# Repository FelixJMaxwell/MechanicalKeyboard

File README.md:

# Teclados Mecanicos
Repositorio creado para contener proyectos relacionados al super costoso hobby de los teclados mecanicos.

Siguiendo los tutoriales por parte de ai03 y MasterZen
 - [PCB Designer Guide](https://wiki.ai03.com/books/pcb-design/chapter/pcb-designer-guide)
 - [Designing a keyboard from scratch](https://www.masterzen.fr/2020/05/03/designing-a-keyboard-part-1/)

No considero ninguna de los dos anterior mejor que el otro pues se complementan en diferentes aspectos.

<br>
<br>
  
# Macropad

Foot print con marca para cada tecla  
  
Footprint sin marca para cada tecla  

<br>
<br>
  
# Split keyboard

<br>
<br>

# Cuarenta Keyboard

La PCB anterior contiene tres errores

1.- Un switch no esta conectado al diodo correspondiente

2.- Hizo falta poner una via para conectar tres switches a su columna correspondiente

3.- El encoder esta conectado en la misma posicion del ultimo switch de su columna, se de agregar a una nueva fila.

Esta PCB la envie a producción con JLCPCB antes de ver los errores por lo que llegaron cinco placas todas con los tres errores anteriores.

Errores en la PCB, corregidos con puentes usando barillas de laton.

Encoder + switch conectado a otro pin del Arduino micro al mismo tiempo que se puentean los adaptadores para hotswap 

Se conecta el adaptador hotswap al diodo correspondiente

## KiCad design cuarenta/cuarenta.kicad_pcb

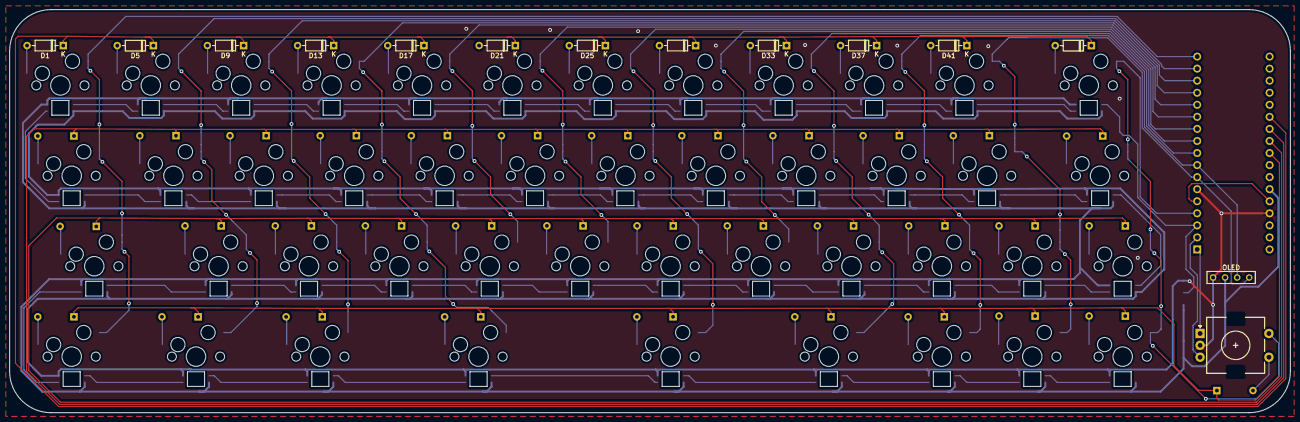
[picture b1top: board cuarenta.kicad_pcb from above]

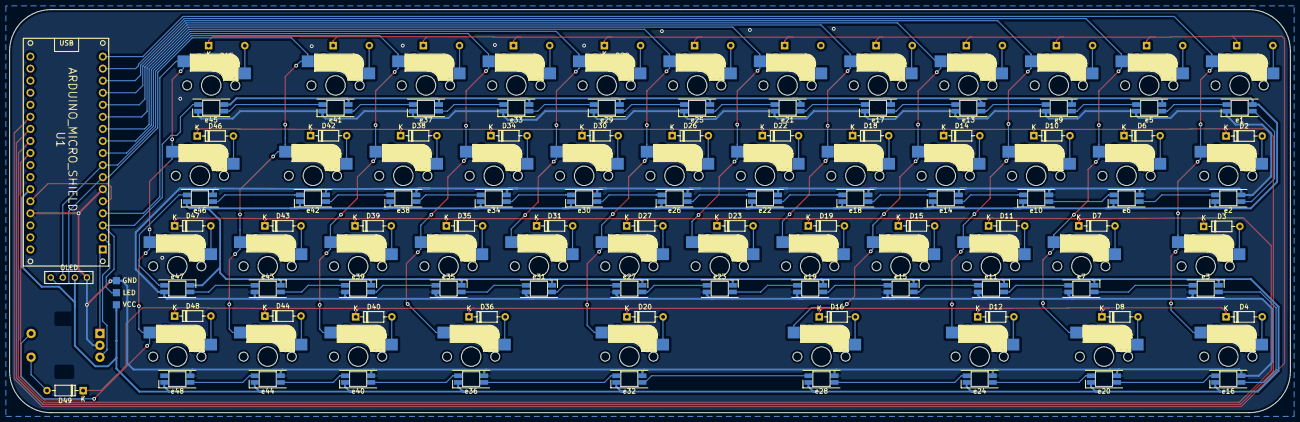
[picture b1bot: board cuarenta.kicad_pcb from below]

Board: 2 copper layers, 269.8 x 84.9 mm, 140 parts (81 on the bottom side), 111 nets.

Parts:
D1, D2, D3, D4, D5, D6, D7, D8, D9, D10, D11, D12, D13, D14, D15, D16, D17, D18, D19, D20, D21, D22, D23, D25, D26, D27, D29, D30, D31, D33, D34, D35, D36, D37, D38, D39, D40, D41, D42, D43, D44, D45, D46, D47, D48, D49: 1N4148; D_DO-35_SOD27_P7.62mm_Horizontal
J1: LED; StripLED_1side
OL1: OLED
SW1, SW2, SW3, SW4, SW5, SW6, SW7, SW8, SW9, SW10, SW11, SW12, SW13, SW14, SW15, SW16, SW17, SW18, SW19, SW20, SW21, SW22, SW23, SW25, SW26, SW27, SW29, SW30, SW31, SW33, SW34, SW35, SW36, SW37, SW38, SW39, SW40, SW41, SW42, SW43, SW44, SW45, SW46, SW47, SW48: SW_Push; CherryMX_Hotswap
SW49: Rotary_Encoder_Switch; RotaryEncoder_EC11
U1: ARDUINO_MICRO_SHIELD
e1, e2, e3, e5, e6, e7, e9, e10, e11, e13, e14, e15, e16, e17, e18, e19, e20, e21, e22, e23, e24, e25, e26, e27, e28, e29, e30, e31, e32, e33, e34, e35, e36, e37, e38, e39, e40, e41, e42, e43, e44, e45, e46, e47, e48: e; YS-SK6812MINI-E_2

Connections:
Col0: SW1.2, SW2.2, SW3.2, SW4.2, U1.12
Col1: SW5.2, SW6.2, SW7.2, SW8.2, U1.11
Col2: SW9.2, SW10.2, SW11.2, SW12.2, U1.10
Col3: SW13.2, SW14.2, SW15.2, SW16.2, U1.9
Col4: SW17.2, SW18.2, SW19.2, U1.8
Col5: SW21.2, SW22.2, SW23.2, U1.7
Col6: SW20.2, SW25.2, SW26.2, SW27.2, U1.6
Col7: SW29.2, SW30.2, SW31.2, U1.5
Col8: SW33.2, SW34.2, SW35.2, SW36.2, U1.4
Col9: OL1.3, SW37.2, SW38.2, SW39.2, SW40.2, U1.3
Col10: OL1.4, SW41.2, SW42.2, SW43.2, SW44.2, U1.2
Col11: SW45.2, SW46.2, SW47.2, SW48.2, SW49.S2, U1.RX
GND: J1.3, OL1.1, SW49.C, U1.GND, e1.3, e2.1, e3.1, e5.3, e6.1, e7.1, e9.3, e10.1, e11.1, e13.3, e14.1, e15.1, e16.1, e17.3, e18.1, e19.1, e20.1, e21.3, e22.1, e23.1, e24.1, e25.3, e26.1, e27.1, e28.1, e29.3, e30.1, e31.1, e32.1, e33.3, e34.1, e35.1, e36.1, e37.3, e38.1, e39.1, e40.1, e41.3, e42.1, e43.1, e44.1, e45.3, e46.1, e47.1, e48.1
LED: J1.2, U1.TX, e45.4
unnamed: D1.2, SW1.1
unnamed: D2.2, SW2.1
unnamed: D3.2, SW3.1
unnamed: D4.2, SW4.1
unnamed: D5.2, SW5.1
unnamed: D6.2, SW6.1
unnamed: D7.2, SW7.1
unnamed: D8.2, SW8.1
unnamed: D9.2, SW9.1
unnamed: D10.2, SW10.1
unnamed: D11.2, SW11.1
unnamed: D12.2, SW12.1
unnamed: D13.2, SW13.1
unnamed: D14.2, SW14.1
unnamed: D15.2, SW15.1
unnamed: D16.2, SW16.1
unnamed: D17.2, SW17.1
unnamed: D18.2, SW18.1
unnamed: D19.2, SW19.1
unnamed: D20.2, SW20.1
unnamed: D21.2, SW21.1
unnamed: D22.2, SW22.1
unnamed: D23.2, SW23.1
unnamed: D25.2, SW25.1
unnamed: D26.2, SW26.1
unnamed: D27.2, SW27.1
unnamed: D29.2, SW29.1
unnamed: D30.2, SW30.1
unnamed: D31.2, SW31.1
unnamed: D33.2, SW33.1
unnamed: D34.2, SW34.1
unnamed: D35.2, SW35.1
unnamed: D36.2, SW36.1
unnamed: D37.2, SW37.1
unnamed: D38.2, SW38.1
unnamed: D39.2, SW39.1
unnamed: D40.2, SW40.1
unnamed: D41.2, SW41.1
unnamed: D42.2, SW42.1
unnamed: D43.2, SW43.1
unnamed: D44.2, SW44.1
unnamed: D45.2, SW45.1
unnamed: D46.2, SW46.1
unnamed: D47.2, SW47.1
unnamed: D48.2, SW48.1
unnamed: D49.2, SW49.S1
unnamed: e1.2, e2.2
unnamed: e1.4, e5.2
unnamed: e2.4, e6.2
unnamed: e3.2, e7.4
unnamed: e5.4, e9.2
unnamed: e6.4, e10.2
unnamed: e10.4, e14.2
unnamed: e11.2, e15.4
unnamed: e7.2, e11.4
unnamed: e9.4, e13.2
unnamed: e13.4, e17.2
unnamed: e14.4, e18.2
unnamed: e15.2, e19.4
unnamed: e3.4, e16.2
unnamed: e16.4, e20.2
unnamed: e17.4, e21.2
unnamed: e18.4, e22.2
unnamed: e19.2, e23.4
unnamed: e20.4, e24.2
unnamed: e21.4, e25.2
unnamed: e22.4, e26.2
unnamed: e23.2, e27.4
unnamed: e24.4, e28.2
unnamed: e25.4, e29.2
unnamed: e26.4, e30.2
unnamed: e27.2, e31.4
unnamed: e28.4, e32.2
unnamed: e29.4, e33.2
unnamed: e30.4, e34.2
unnamed: e31.2, e35.4
unnamed: e32.4, e36.2
unnamed: e33.4, e37.2
unnamed: e34.4, e38.2
unnamed: e35.2, e39.4
unnamed: e36.4, e40.2
unnamed: e37.4, e41.2
unnamed: e38.4, e42.2
unnamed: e39.2, e43.4
unnamed: e40.4, e44.2
unnamed: e41.4, e45.2
unnamed: e42.4, e46.2
unnamed: e43.2, e47.4
unnamed: e44.4, e48.2
unnamed: e46.4, e47.2
Row0: D1.1, D5.1, D9.1, D13.1, D17.1, D21.1, D25.1, D29.1, D33.1, D37.1, D41.1, D45.1, U1.A2
Row1: D2.1, D6.1, D10.1, D14.1, D18.1, D22.1, D26.1, D30.1, D34.1, D38.1, D42.1, D46.1, U1.A3
Row2: D3.1, D7.1, D11.1, D15.1, D19.1, D23.1, D27.1, D31.1, D35.1, D39.1, D43.1, D47.1, U1.A4
Row3: D4.1, D8.1, D12.1, D16.1, D20.1, D36.1, D40.1, D44.1, D48.1, D49.1, U1.A5
VCC: J1.1, OL1.2, U1.5V, e1.1, e2.3, e3.3, e5.1, e6.3, e7.3, e9.1, e10.3, e11.3, e13.1, e14.3, e15.3, e16.3, e17.1, e18.3, e19.3, e20.3, e21.1, e22.3, e23.3, e24.3, e25.1, e26.3, e27.3, e28.3, e29.1, e30.3, e31.3, e32.3, e33.1, e34.3, e35.3, e36.3, e37.1, e38.3, e39.3, e40.3, e41.1, e42.3, e43.3, e44.3, e45.1, e46.3, e47.3, e48.3
en1: SW49.B, U1.SS
en2: SW49.A, U1.MO

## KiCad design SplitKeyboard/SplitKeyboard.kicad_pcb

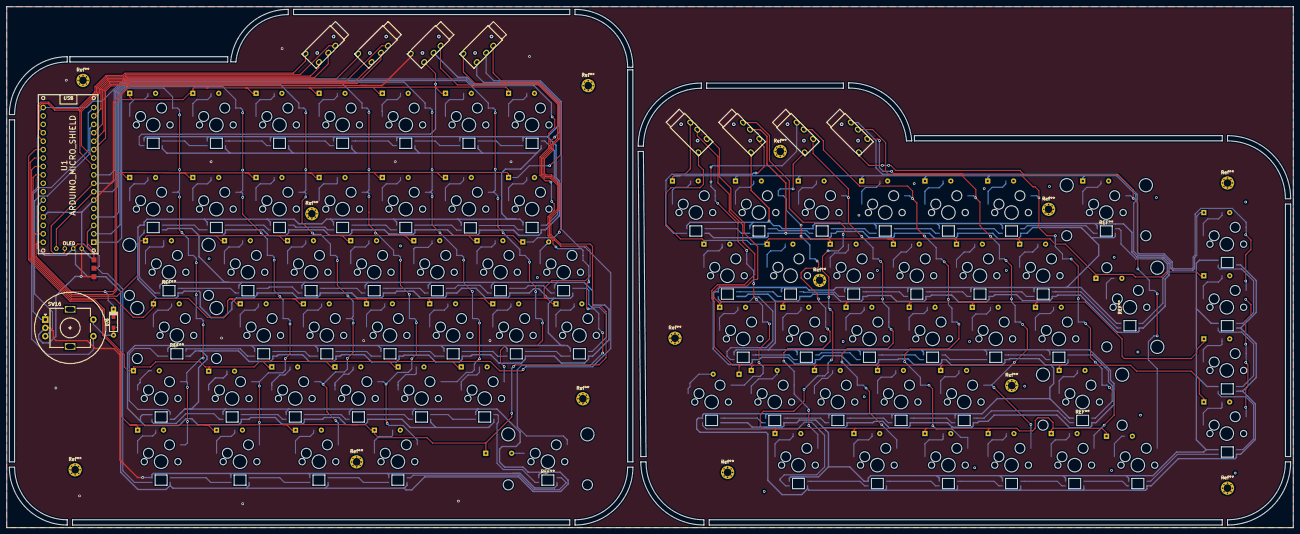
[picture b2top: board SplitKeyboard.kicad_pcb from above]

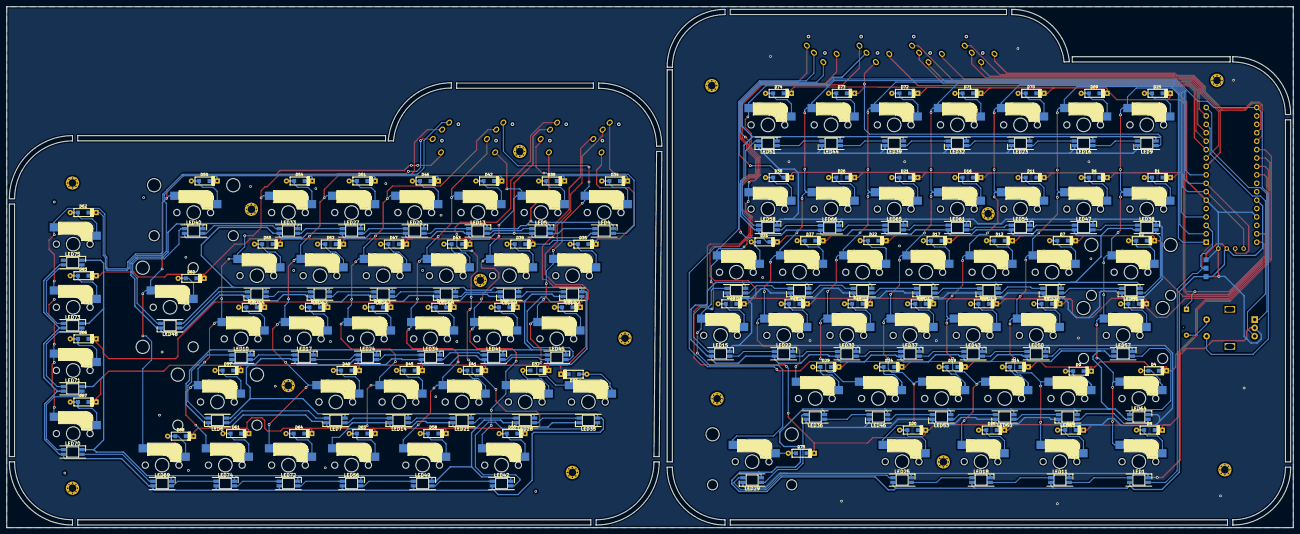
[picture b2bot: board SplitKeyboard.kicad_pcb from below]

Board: 2 copper layers, 388.1 x 157.1 mm, 252 parts (150 on the bottom side), 105 nets.

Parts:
D1, D2, D3, D4, D5, D6, D7, D8, D9, D10, D11, D12, D13, D14, D15, D16, D17, D18, D19, D20, D21, D22, D23, D24, D25, D26, D27, D28, D29, D30, D31, D32, D33, D34, D35, D36, D37, D38, D39, D40, D41, D42, D43, D44, D45, D46, D47, D48, D49, D50, D51, D52, D53, D54, D55, D56, D57, D58, D59, D60, D61, D62, D63, D64, D65, D66, D67, D68, D69, D70, D71, D72, D73, D74, D75, D76: 1N4148; D_SOD123_axial
J1: LED; StripLED_rev
JTRRS1, JTRRS2, JTRRS3, JTRRS4, JTRRS5, JTRRS6, JTRRS7, JTRRS8: 4PIN; TRRS-PJ-320A
LED1, LED2, LED3, LED4, LED5, LED6, LED7, LED8, LED9, LED10, LED11, LED12, LED13, LED14, LED15, LED16, LED17, LED18, LED19, LED20, LED21, LED22, LED23, LED24, LED25, LED26, LED27, LED28, LED29, LED30, LED31, LED32, LED33, LED34, LED35, LED36, LED37, LED38, LED39, LED40, LED41, LED42, LED43, LED44, LED45, LED46, LED47, LED48, LED49, LED50, LED51, LED52, LED53, LED54, LED55, LED56, LED57, LED58, LED59, LED60, LED61, LED62, LED63, LED64, LED65, LED66, LED67, LED68, LED69, LED70, LED71, LED72, LED73, LED74, LED75: YS-SK6812MINI-E; YS-SK6812MINI-E_2
P2: OLED; OLED_v2
Ref**: Val**; M2_HOLE_v3
Ref**#2, Ref**#3, Ref**#4, Ref**#5, Ref**#6, Ref**#7, Ref**#8, Ref**#9, Ref**#10, Ref**#11, Ref**#12, Ref**#13, Ref**#14: Val**; M2_HOLE_v3
SW0, SW1, SW2, SW3, SW4, SW5, SW6, SW7, SW8, SW9, SW14, SW15: SW_Push; CherryMX_Hotswap
SW10: SW_DownArrow; CherryMX_Hotswap
SW13: SW_RightArrow; CherryMX_Hotswap
SW16: Rotary_Encoder_Switch; RotaryEncoder_Alps_EC11E-Switch_Vertical_H20mm
SW+1: SW_Push; CherryMX_Hotswap
SWBarrita1: SW_Push; CherryMX_Hotswap
SWCtrlright1: SW_Push; CherryMX_Hotswap
SWF2, SWF4, SWF5, SWF6, SWF8, SWF12: SW_Push; CherryMX_Hotswap
SWLeftArrow1: SW_Push; CherryMX_Hotswap
SWUpArrow1: SW_Push; CherryMX_Hotswap
SWa1: SW_Push; CherryMX_Hotswap
SWaltgr1: SW_Push; CherryMX_Hotswap
SWaltleft1: SW_Push; CherryMX_Hotswap
SWb1: SW_Push; CherryMX_Hotswap
SWbackslash1: SW_Push; CherryMX_Hotswap
SWbloqmayus1: SW_Push; CherryMX_Hotswap
SWc1: SW_Push; CherryMX_Hotswap
SWcomilla1: SW_Push; CherryMX_Hotswap
SWcomma1: SW_Push; CherryMX_Hotswap
SWctrl1: SW_Push; CherryMX_Hotswap
SWd1: SW_Push; CherryMX_Hotswap
SWe1: SW_Push; CherryMX_Hotswap
SWend1: SW_Push; CherryMX_Hotswap
SWenter1: SW_Push; CherryMX_Hotswap
SWesc1: SW_Push; CherryMX_Hotswap
SWf1: SW_Push; CherryMX_Hotswap
SWfn1: SW_Push; CherryMX_Hotswap
SWg1: SW_Push; CherryMX_Hotswap
SWguion1: SW_Push; CherryMX_Hotswap
SWh1: SW_Push; CherryMX_Hotswap
SWhome1: SW_Push; CherryMX_Hotswap
SWi1: SW_Push; CherryMX_Hotswap
SWj1: SW_Push; CherryMX_Hotswap
SWk1: SW_Push; CherryMX_Hotswap
SWl1: SW_Push; CherryMX_Hotswap
SWm1: SW_Push; CherryMX_Hotswap
SWn1: SW_Push; CherryMX_Hotswap
SWo1: SW_Push; CherryMX_Hotswap
SWp1: SW_Push; CherryMX_Hotswap
SWpgdown1: SW_Push; CherryMX_Hotswap
SWpgup1: SW_Push; CherryMX_Hotswap
SWpunto1: SW_Push; CherryMX_Hotswap
SWq1: SW_Push; CherryMX_Hotswap
SWr1: SW_Push; CherryMX_Hotswap
SWs1: SW_Push; CherryMX_Hotswap
SWshift1: SW_Push; CherryMX_Hotswap
SWshiftright1: SW_Push; CherryMX_Hotswap
SWsigno1: SW_Push; CherryMX_Hotswap
SWspace1: SW_Push; CherryMX_Hotswap
SWt1: SW_Push; CherryMX_Hotswap
SWtab1: SW_Push; CherryMX_Hotswap
SWu1: SW_Push; CherryMX_Hotswap
SWv1: SW_Push; CherryMX_Hotswap
SWw1: SW_Push; CherryMX_Hotswap
SWwin1: SW_Push; CherryMX_Hotswap
SWx1: SW_Push; CherryMX_Hotswap
SWy1: SW_Push; CherryMX_Hotswap
SWz1: SW_Push; CherryMX_Hotswap
SW{1: SW_Push; CherryMX_Hotswap
SW}1: SW_Push; CherryMX_Hotswap
U1: ARDUINO_MICRO_SHIELD

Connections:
Columna2: JTRRS4.1, U1.A1
Columna3: JTRRS4.2, U1.5
Columna4: JTRRS4.3, U1.6
Columna5: JTRRS3.3, U1.7
Columna6: JTRRS3.2, U1.8
Columna7: JTRRS3.1, U1.11
Columna8: JTRRS3.4, U1.9
Columna9: SW6.2, SW16.S1, SWF12.2, SWh1.2, SWspace1.2, SWy1.2, U1.13
Columna10: SW5.2, SWF8.2, SWb1.2, SWg1.2, SWt1.2, U1.4
Columna11: P2.2, SW4.2, SWF6.2, SWf1.2, SWr1.2, SWv1.2, U1.3
Columna12: P2.1, SW3.2, SWF5.2, SWc1.2, SWd1.2, SWe1.2, SWfn1.2, U1.2
Columna13: SW2.2, SWF4.2, SWaltleft1.2, SWs1.2, SWw1.2, SWx1.2, U1.RX
Columna14: SW1.2, SWF2.2, SWa1.2, SWq1.2, SWwin1.2, SWz1.2, U1.SS
Columna15: SWBarrita1.2, SWbloqmayus1.2, SWctrl1.2, SWesc1.2, SWshift1.2, SWtab1.2, U1.MO
Columna16: JTRRS4.4, U1.A0
Fila0: D25.1, D69.1, D70.1, D71.1, D72.1, D73.1, D74.1, D76.1, U1.SCK
Fila1: D1.1, D6.1, D11.1, D16.1, D21.1, D26.1, D30.1, JTRRS5.4, U1.MI
Fila3: D3.1, D8.1, D13.1, D18.1, D23.1, D28.1, D32.1, JTRRS5.2, U1.A4
Fila4: D4.1, D9.1, D14.1, D19.1, D24.1, D29.1, JTRRS5.3, U1.A3
Fila5: D5.1, D10.1, D15.1, D20.1, D75.1, JTRRS6.4, U1.A2
Fila6: D2.1, D7.1, D12.1, D17.1, D22.1, D27.1, D31.1, JTRRS5.1, U1.A5
GND: J1.3, JTRRS6.1, LED1.3, LED2.3, LED3.3, LED8.3, LED9.3, LED11.3, LED12.3, LED15.3, LED16.3, LED18.3, LED19.3, LED22.3, LED23.3, LED25.3, LED26.3, LED29.3, LED30.3, LED31.3, LED32.3, LED36.3, LED37.3, LED38.3, LED39.3, LED43.3, LED44.3, LED46.3, LED47.3, LED50.3, LED51.3, LED53.3, LED54.3, LED57.3, LED58.3, LED60.3, LED61.3, LED63.3, LED64.3, LED65.3, LED66.3, P2.4, SW16.C, U1.GND
LED: J1.2, LED1.4, U1.TX
LEDTRRS: JTRRS6.2, LED9.2
unnamed: D1.2, SWBarrita1.1
unnamed: D2.2, SWtab1.1
unnamed: D3.2, SWbloqmayus1.1
unnamed: D4.2, SWshift1.1
unnamed: D5.2, SWctrl1.1
unnamed: D6.2, SW1.1
unnamed: D7.2, SWq1.1
unnamed: D8.2, SWa1.1
unnamed: D9.2, SWz1.1
unnamed: D10.2, SWwin1.1
unnamed: D11.2, SW2.1
unnamed: D12.2, SWw1.1
unnamed: D13.2, SWs1.1
unnamed: D14.2, SWx1.1
unnamed: D15.2, SWaltleft1.1
unnamed: D16.2, SW3.1
unnamed: D17.2, SWe1.1
unnamed: D18.2, SWd1.1
unnamed: D19.2, SWc1.1
unnamed: D20.2, SWfn1.1
unnamed: D21.2, SW4.1
unnamed: D22.2, SWr1.1
unnamed: D23.2, SWf1.1
unnamed: D24.2, SWv1.1
unnamed: D25.2, SWesc1.1
unnamed: D26.2, SW5.1
unnamed: D27.2, SWt1.1
unnamed: D28.2, SWg1.1
unnamed: D29.2, SWb1.1
unnamed: D30.2, SW6.1
unnamed: D31.2, SWy1.1
unnamed: D32.2, SWh1.1
unnamed: D69.2, SWF2.1
unnamed: D70.2, SWF4.1
unnamed: D71.2, SWF5.1
unnamed: D72.2, SWF6.1
unnamed: D73.2, SWF8.1
unnamed: D74.2, SWF12.1
unnamed: D75.2, SWspace1.1
unnamed: D76.2, SW16.S2
unnamed: LED1.2, LED11.4
unnamed: LED2.2, LED3.4
unnamed: LED2.4, LED8.2
unnamed: LED11.2, LED18.4
unnamed: LED12.2, LED19.4
unnamed: LED3.2, LED12.4
unnamed: LED8.4, LED15.2
unnamed: LED15.4, LED22.2
unnamed: LED9.4, LED16.2
unnamed: LED16.4, LED23.2
unnamed: LED18.2, LED25.4
unnamed: LED19.2, LED26.4
unnamed: LED22.4, LED30.2
unnamed: LED23.4, LED32.2
unnamed: LED25.2, LED29.4
unnamed: LED26.2, LED31.4
unnamed: LED29.2, LED36.4
unnamed: LED30.4, LED37.2
unnamed: LED31.2, LED38.4
unnamed: LED32.4, LED39.2
unnamed: LED36.2, LED46.4
unnamed: LED37.4, LED43.2
unnamed: LED38.2, LED47.4
unnamed: LED39.4, LED44.2
unnamed: LED43.4, LED50.2
unnamed: LED44.4, LED51.2
unnamed: LED46.2, LED53.4
unnamed: LED47.2, LED54.4
unnamed: LED50.4, LED57.2
unnamed: LED51.4, LED58.2
unnamed: LED53.2, LED60.4
unnamed: LED54.2, LED61.4
unnamed: LED57.4, LED64.2
unnamed: LED58.4, LED66.2
unnamed: LED60.2, LED63.4
unnamed: LED61.2, LED65.4
unnamed: LED63.2, LED64.4
unnamed: LED65.2, LED66.4
VCC: J1.1, JTRRS6.3, LED1.1, LED2.1, LED3.1, LED8.1, LED9.1, LED11.1, LED12.1, LED15.1, LED16.1, LED18.1, LED19.1, LED22.1, LED23.1, LED25.1, LED26.1, LED29.1, LED30.1, LED31.1, LED32.1, LED36.1, LED37.1, LED38.1, LED39.1, LED43.1, LED44.1, LED46.1, LED47.1, LED50.1, LED51.1, LED53.1, LED54.1, LED57.1, LED58.1, LED60.1, LED61.1, LED63.1, LED64.1, LED65.1, LED66.1, P2.3, U1.5V
en1: SW16.B, U1.10
en2: SW16.A, U1.12

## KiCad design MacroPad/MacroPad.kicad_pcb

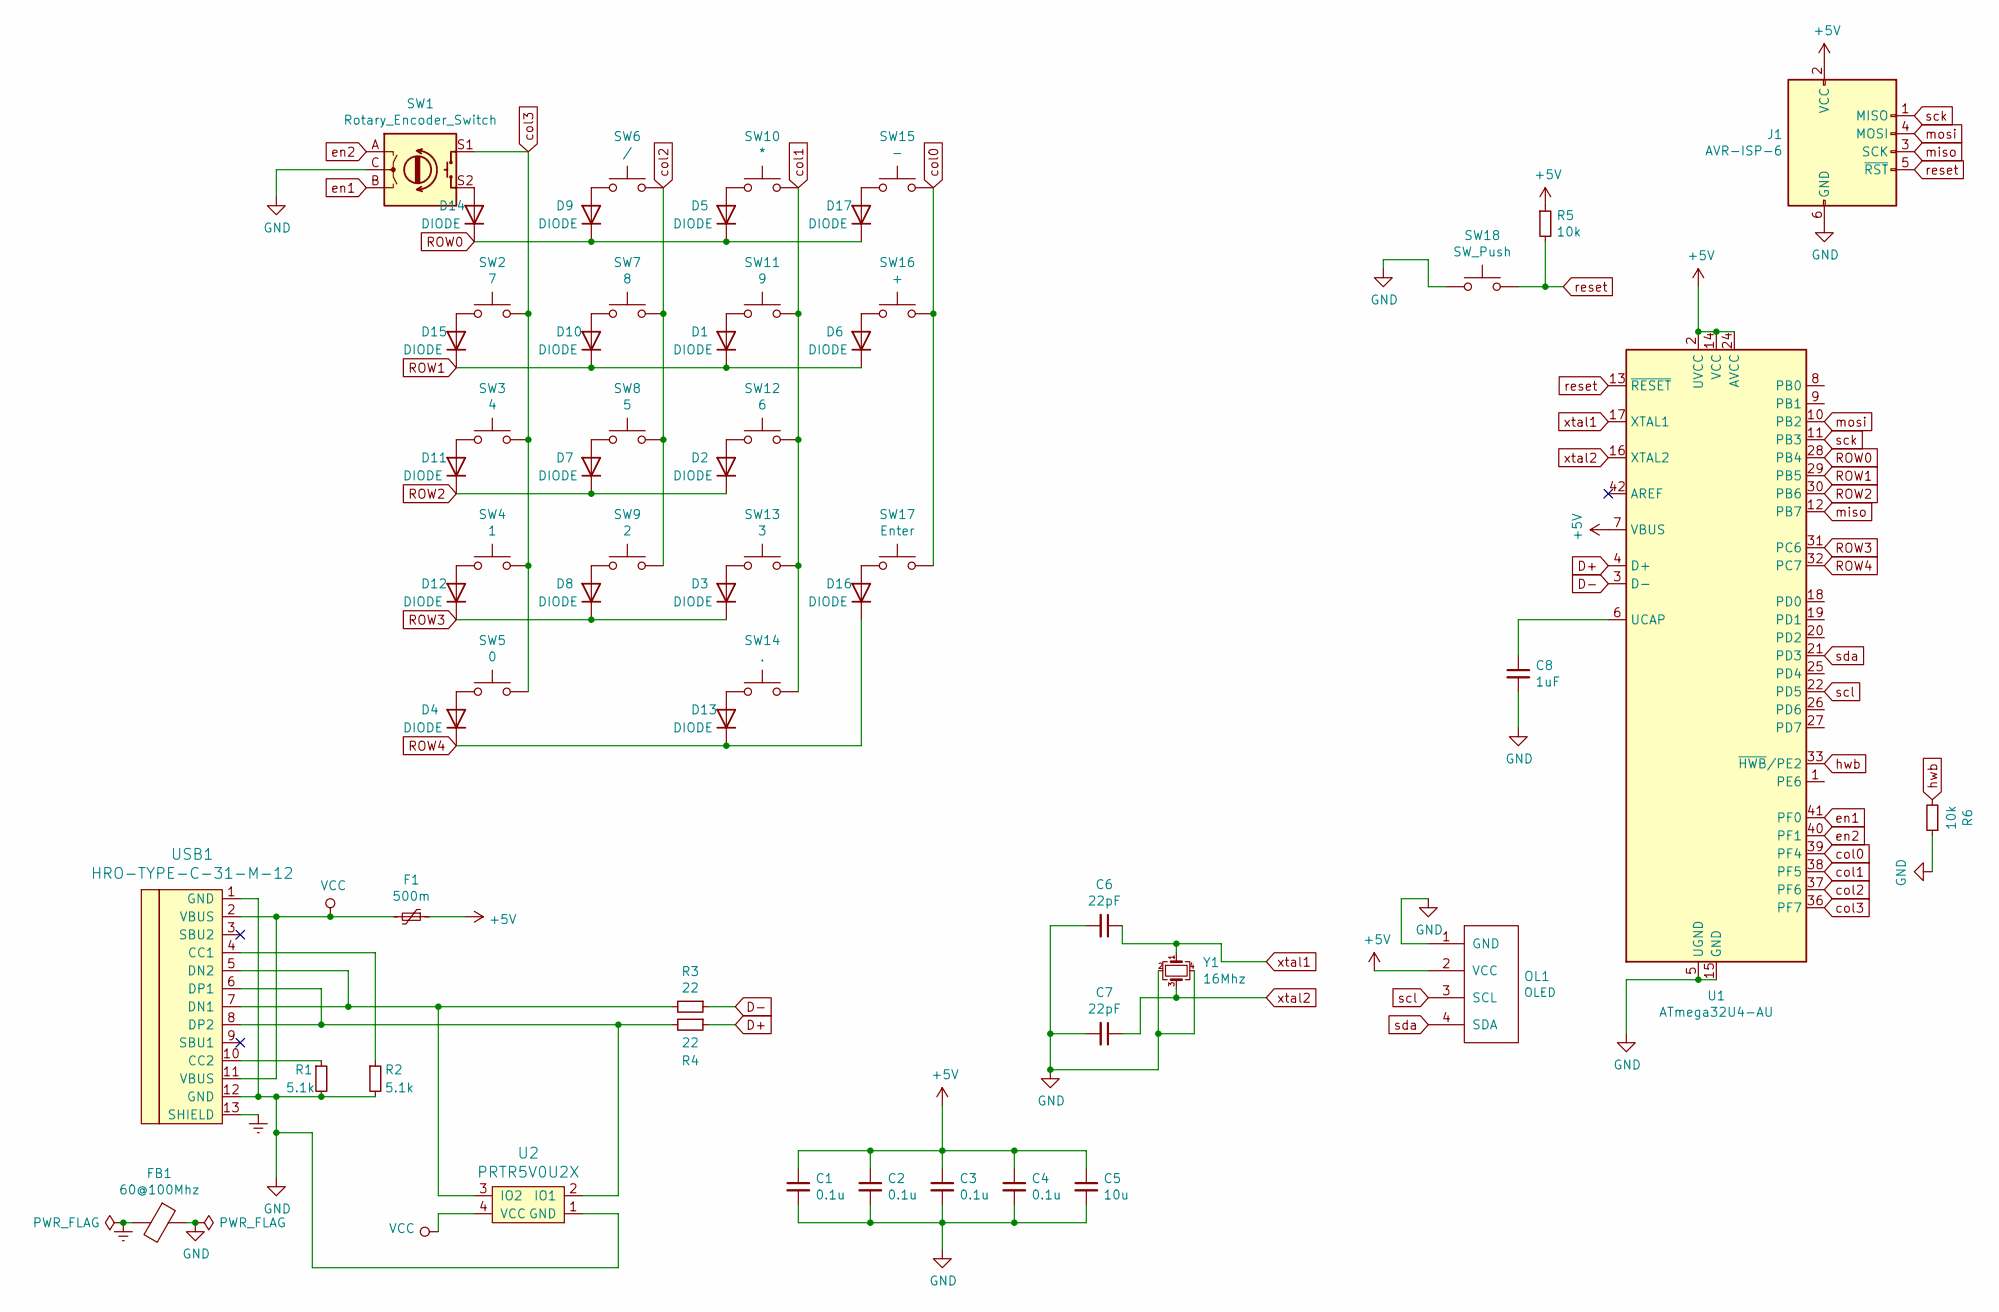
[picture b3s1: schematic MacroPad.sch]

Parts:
C1, C2, C3, C4: 0.1u; C_0805_2012Metric_Pad1.15x1.40mm_HandSolder
C5: 10u; C_0805_2012Metric_Pad1.15x1.40mm_HandSolder
C6, C7: 22pF; C_0805_2012Metric_Pad1.15x1.40mm_HandSolder
C8: 1uF; C_0805_2012Metric_Pad1.15x1.40mm_HandSolder
D1, D2, D3, D4, D5, D6, D7, D8, D9, D10, D11, D12, D13, D14, D15, D16, D17: DIODE; D_SOD123_axial
F1: 500m; Fuse_1206_3216Metric_Pad1.42x1.75mm_HandSolder
FB1: 60@100Mhz; L_0805_2012Metric_Pad1.15x1.40mm_HandSolder
J1: AVR-ISP-6; AVR_ICSP_3x2
OL1: OLED; SSD1306-0.91-OLED-4pin-128x32
R1, R2: 5.1k; R_0805_2012Metric_Pad1.15x1.40mm_HandSolder
R3, R4: 22; R_0805_2012Metric_Pad1.15x1.40mm_HandSolder
R5, R6: 10k; R_0805_2012Metric_Pad1.15x1.40mm_HandSolder
SW1: Rotary_Encoder_Switch; RotaryEncoder_Alps_EC11E-Switch_Vertical_H20mm
SW2: 7; Kailh_socket_MX
SW3: 4; Kailh_socket_MX
SW4: 1; Kailh_socket_MX
SW5: 0; Kailh_socket_MX
SW6: /; Kailh_socket_MX
SW7: 8; Kailh_socket_MX
SW8: 5; Kailh_socket_MX
SW9: 2; Kailh_socket_MX
SW10: *; Kailh_socket_MX
SW11: 9; Kailh_socket_MX
SW12: 6; Kailh_socket_MX
SW13: 3; Kailh_socket_MX
SW14: .; Kailh_socket_MX
SW15: -; Kailh_socket_MX
SW16: +; Kailh_socket_MX
SW17: Enter; Kailh_socket_MX
SW18: SW_Push; SW_SPST_SKQG_WithStem
U1: ATmega32U4-AU; TQFP-44_10x10mm_P0.8mm
U2: PRTR5V0U2X; tm-kicad-library-master_tm-kicad-lib.pretty_PRTR5V0U2X,215
USB1: HRO-TYPE-C-31-M-12; HRO-TYPE-C-31-M-12-HandSoldering
Y1: 16Mhz; Crystal_SMD_3225-4Pin_3.2x2.5mm_HandSoldering

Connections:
+5V: C1.1, C2.1, C3.1, C4.1, C5.1, F1.1, J1.2 (VCC), OL1.2 (VCC), R5.1, U1.2 (UVCC), U1.7 (VBUS), U1.14 (VCC), U1.24 (AVCC), U1.34 (VCC), U1.44 (AVCC)
D+: R4.1, U1.4 (D+)
D-: R3.1, U1.3 (D-)
Earth: FB1.2, USB1.13 (SHIELD)
GND: C1.2, C2.2, C3.2, C4.2, C5.2, C6.2, C7.2, C8.2, FB1.1, J1.6 (GND), OL1.1 (GND), R1.2, R2.2, R6.1, SW1.C, SW18.1, U1.5 (UGND), U1.15 (GND), U1.23 (GND), U1.35 (GND), U1.43 (GND), U2.1 (GND), USB1.1 (GND), USB1.12 (GND), Y1.2, Y1.4
unnamed: C8.1, U1.6 (UCAP)
unnamed: D1.1 (A), SW11.1
unnamed: D2.1 (A), SW12.1
unnamed: D3.1 (A), SW13.1
unnamed: D4.1 (A), SW5.1
unnamed: D5.1 (A), SW10.1
unnamed: D6.1 (A), SW16.1
unnamed: D7.1 (A), SW8.1
unnamed: D8.1 (A), SW9.1
unnamed: D9.1 (A), SW6.1
unnamed: D10.1 (A), SW7.1
unnamed: D11.1 (A), SW3.1
unnamed: D12.1 (A), SW4.1
unnamed: D13.1 (A), SW14.1
unnamed: D14.1 (A), SW1.S2
unnamed: D15.1 (A), SW2.1
unnamed: D16.1 (A), SW17.1
unnamed: D17.1 (A), SW15.1
unnamed: R1.1, USB1.10 (CC2)
unnamed: R2.1, USB1.4 (CC1)
unnamed: R3.2, U2.3 (IO2), USB1.5 (DN2), USB1.7 (DN1)
unnamed: R4.2, U2.2 (IO1), USB1.6 (DP1), USB1.8 (DP2)
ROW0: D5.2 (K), D9.2 (K), D14.2 (K), D17.2 (K), U1.28 (PB4)
ROW1: D1.2 (K), D6.2 (K), D10.2 (K), D15.2 (K), U1.29 (PB5)
ROW2: D2.2 (K), D7.2 (K), D11.2 (K), U1.30 (PB6)
ROW3: D3.2 (K), D8.2 (K), D12.2 (K), U1.31 (PC6)
ROW4: D4.2 (K), D13.2 (K), D16.2 (K), U1.32 (PC7)
VCC: F1.2, U2.4 (VCC), USB1.2 (VBUS), USB1.11 (VBUS)
col0: SW15.2, SW16.2, SW17.2, U1.39 (PF4)
col1: SW10.2, SW11.2, SW12.2, SW13.2, SW14.2, U1.38 (PF5)
col2: SW6.2, SW7.2, SW8.2, SW9.2, U1.37 (PF6)
col3: SW1.S1, SW2.2, SW3.2, SW4.2, SW5.2, U1.36 (PF7)
en1: SW1.B, U1.41 (PF0)
en2: SW1.A, U1.40 (PF1)
hwb: R6.2, U1.33 (~HWB~/PE2)
miso: J1.3 (SCK), U1.12 (PB7)
mosi: J1.4 (MOSI), U1.10 (PB2)
reset: J1.5 (~RST), R5.2, SW18.2, U1.13 (~RESET)
sck: J1.1 (MISO), U1.11 (PB3)
scl: OL1.3 (SCL), U1.22 (PD5)
sda: OL1.4 (SDA), U1.21 (PD3)
xtal1: C6.1, U1.17 (XTAL1), Y1.1
xtal2: C7.1, U1.16 (XTAL2), Y1.3

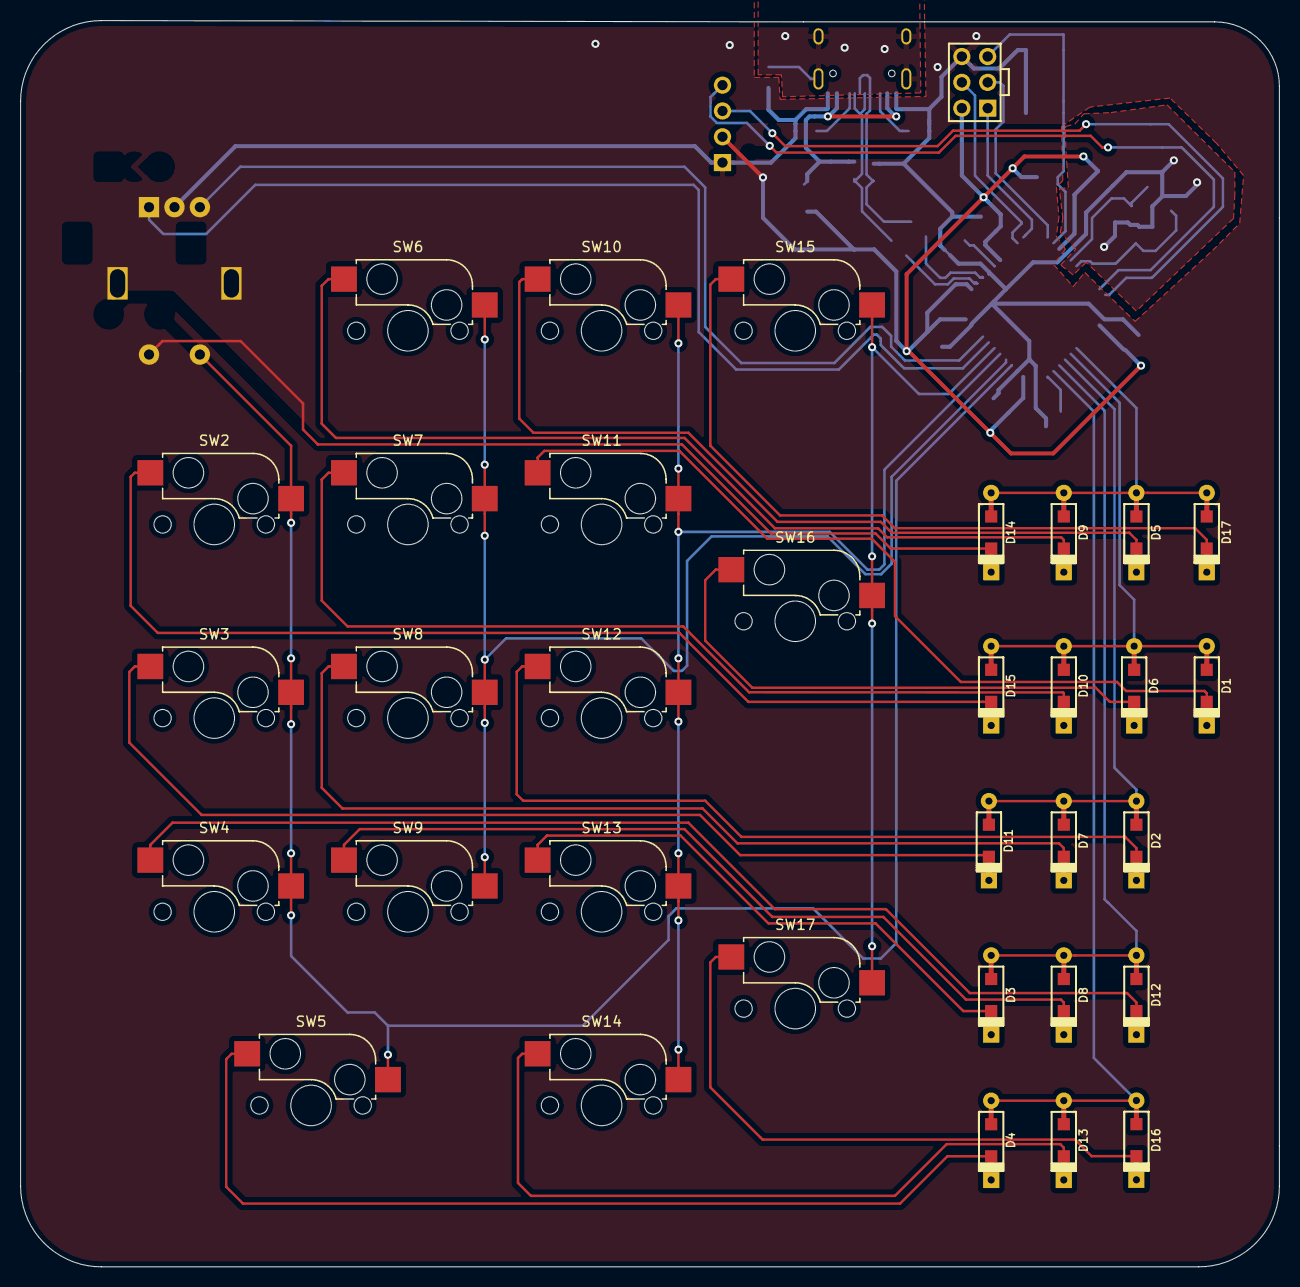
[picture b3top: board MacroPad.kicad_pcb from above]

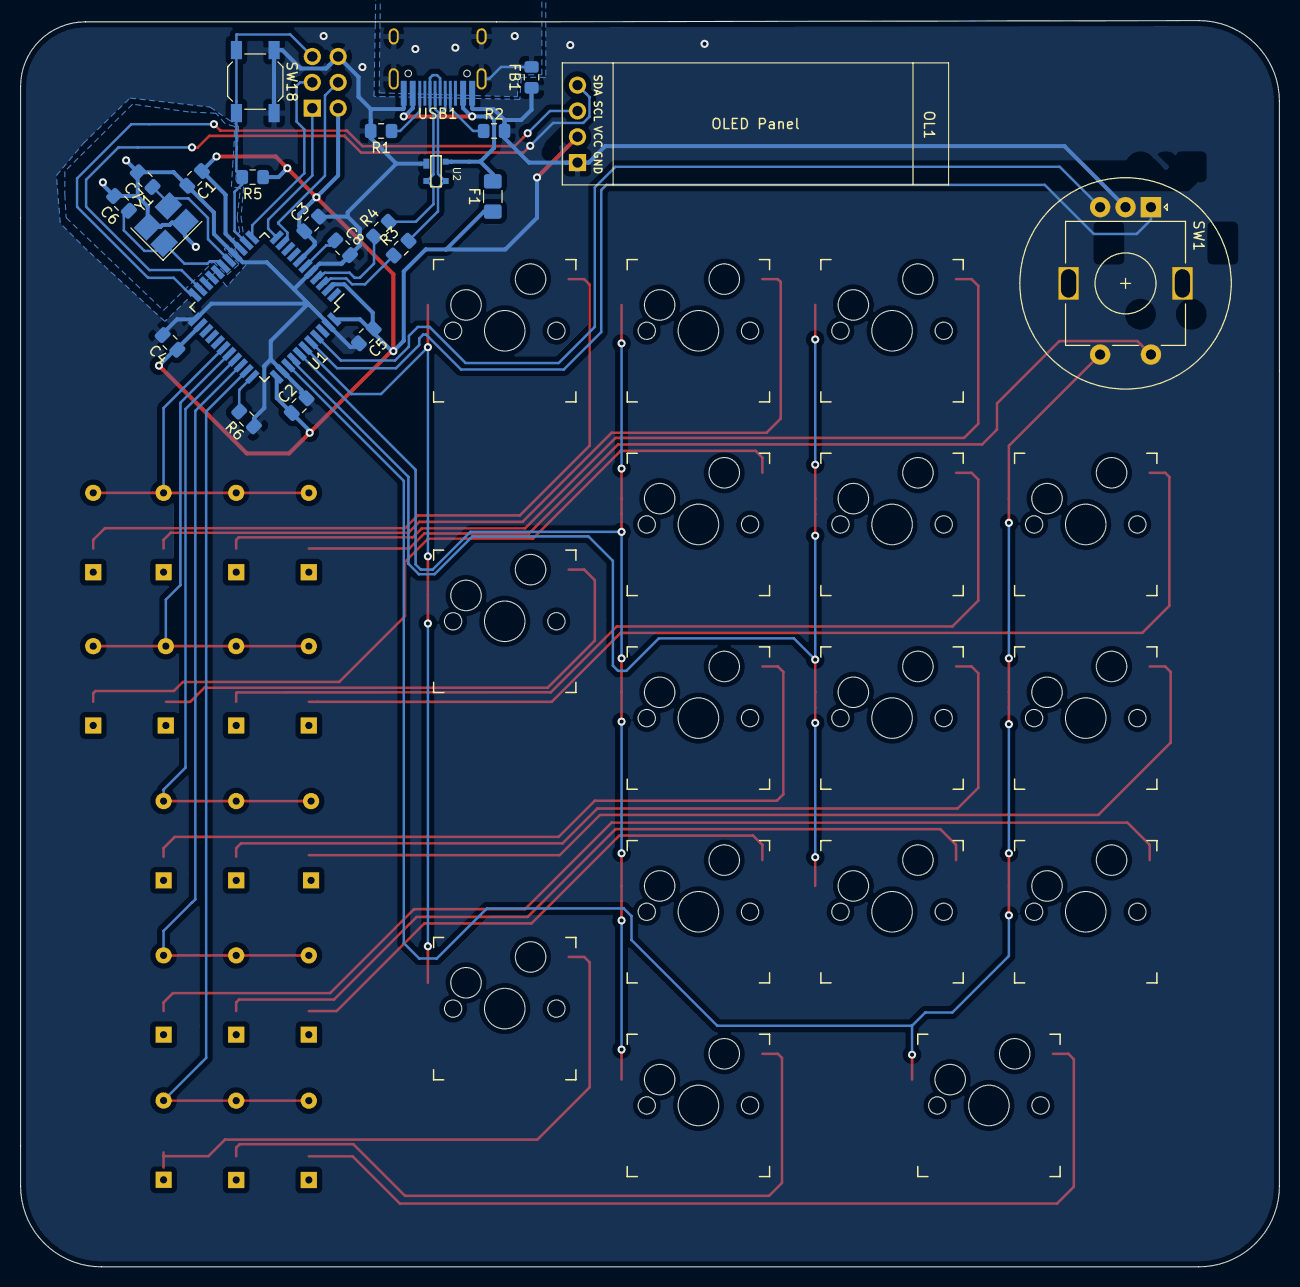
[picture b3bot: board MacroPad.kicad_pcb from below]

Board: 2 copper layers, 123.8 x 122.6 mm, 57 parts (39 on the bottom side), 48 nets.

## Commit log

2021-05-04 rutas v2
2021-05-05 cambiando rutas
2021-05-08 ultimas partes
2021-05-09 final final
2021-05-09 macropad_3 pdf
2021-05-09 cambio de footprint
2021-05-09 footprints preview
2021-05-09 agregado preview del macropad
2021-05-10 cambiado tamaño pistas y vcc oled
2021-06-07 New Footprints
2021-06-07 Folder Modification
2021-06-07 README update
2021-06-07 image route fixed
2021-06-07 image pcbnew added
2021-06-07 added image for split keyboard
2021-06-07 grammar nazi
2021-06-07 image witdh modified
2021-08-08 minivan with RGB knob and led display
2021-09-11 agregada imagen de pcbcnew cuarenta
2021-09-11 agregada evidencia de los errores
2021-09-11 PCB en produccion agregada mas errores
2022-01-11 Agregado 40%
2022-01-13 footprints revueltas
2022-01-13 restaurados archivos 40%
2022-02-03 Endgame D:
2023-05-01 EndGame 30042023
2024-09-25 24092024
